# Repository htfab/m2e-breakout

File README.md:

# Caravel M.2 breakout

Minimalist breakout board for
[M.2 E-key daughtercards](https://github.com/efabless/caravel_board/tree/main/hardware/breakout/caravel-M.2-card-QFN)
shipped with OpenMPW/chipIgnite ICs.

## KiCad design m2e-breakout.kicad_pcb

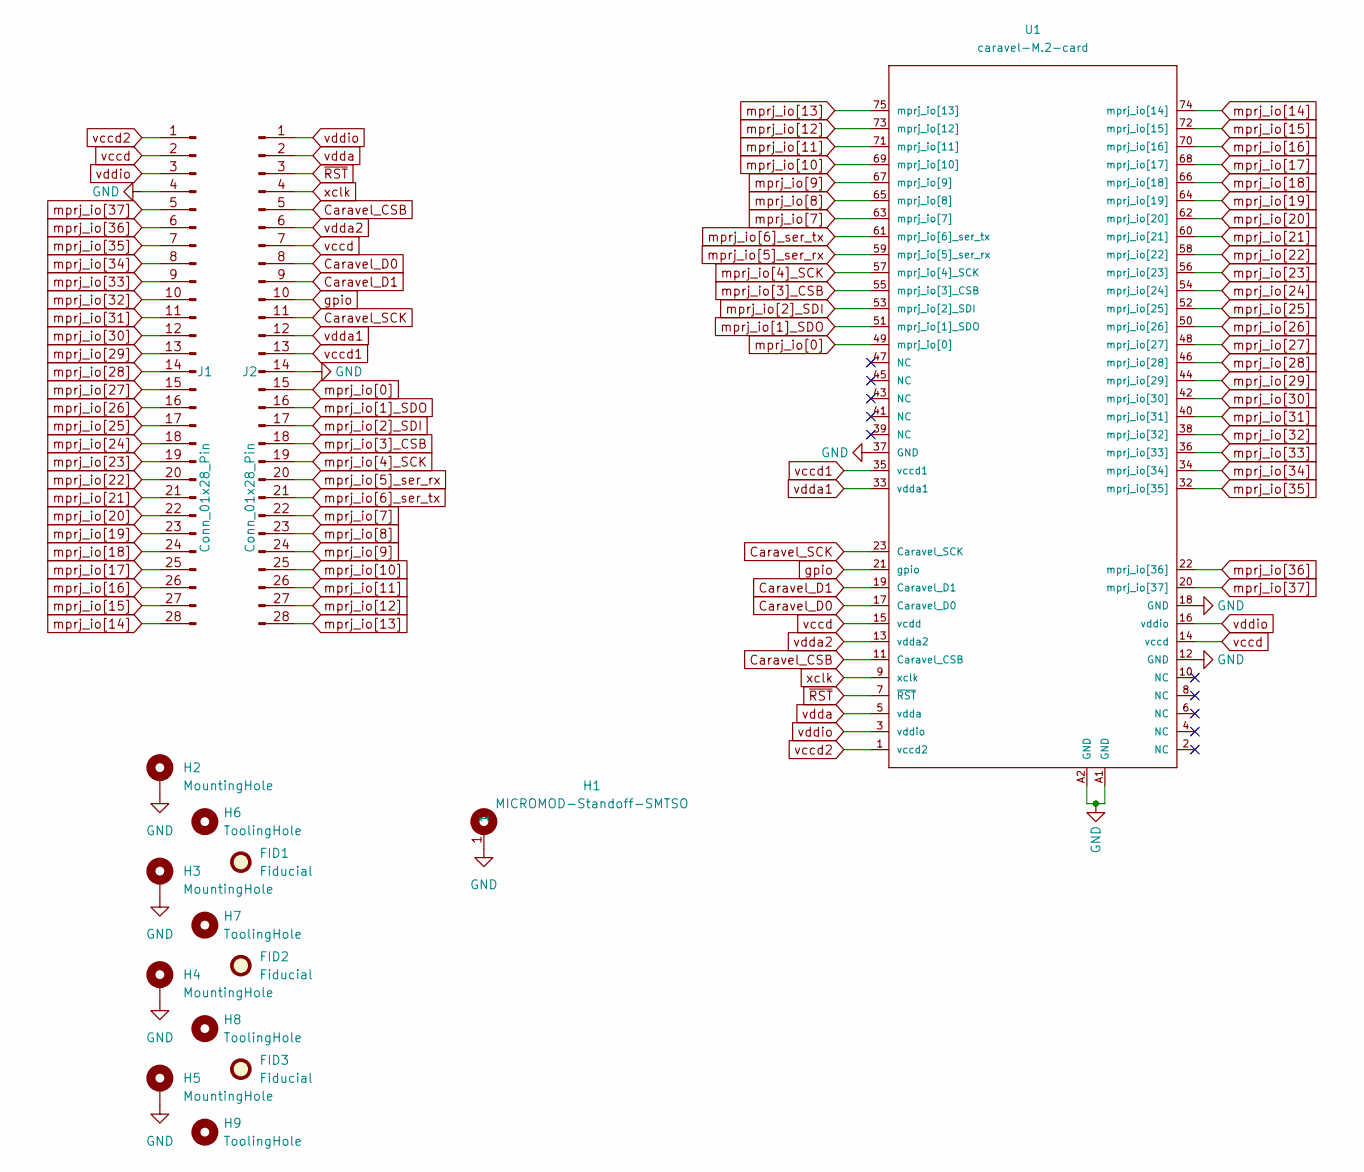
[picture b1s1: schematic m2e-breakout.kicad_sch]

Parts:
FID1, FID2, FID3: Fiducial; Fiducial_1mm_Mask3mm
H1: MICROMOD-Standoff-SMTSO; MicroMod-Standoff-SMTSO; LCSC C2915630
H2, H3, H4, H5: MountingHole; MountingHole_2.7mm_M2.5_Pad_Via
H6, H7, H8, H9: ToolingHole; ToolingHole-JLCSMT
J1, J2: Conn_01x28_Pin; PinHeader_1x28_P2.54mm_Vertical
U1: caravel-M.2-card; M.2-CONNECTOR-E; LCSC C7498141

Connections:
Caravel_CSB: J2.5, U1.11 (Caravel_CSB)
Caravel_D0: J2.8, U1.17 (Caravel_D0)
Caravel_D1: J2.9, U1.19 (Caravel_D1)
Caravel_SCK: J2.11, U1.23 (Caravel_SCK)
GND: H1.1, H2.1, H3.1, H4.1, H5.1, J1.4, J2.14, U1.12 (GND), U1.18 (GND), U1.37 (GND), U1.A1 (GND), U1.A2 (GND)
gpio: J2.10, U1.21 (gpio)
mprj_io[0]: J2.15, U1.49 (mprj_io[0])
mprj_io[1]_SDO: J2.16, U1.51 (mprj_io[1]_SDO)
mprj_io[2]_SDI: J2.17, U1.53 (mprj_io[2]_SDI)
mprj_io[3]_CSB: J2.18, U1.55 (mprj_io[3]_CSB)
mprj_io[4]_SCK: J2.19, U1.57 (mprj_io[4]_SCK)
mprj_io[5]_ser_rx: J2.20, U1.59 (mprj_io[5]_ser_rx)
mprj_io[6]_ser_tx: J2.21, U1.61 (mprj_io[6]_ser_tx)
mprj_io[7]: J2.22, U1.63 (mprj_io[7])
mprj_io[8]: J2.23, U1.65 (mprj_io[8])
mprj_io[9]: J2.24, U1.67 (mprj_io[9])
mprj_io[10]: J2.25, U1.69 (mprj_io[10])
mprj_io[11]: J2.26, U1.71 (mprj_io[11])
mprj_io[12]: J2.27, U1.73 (mprj_io[12])
mprj_io[13]: J2.28, U1.75 (mprj_io[13])
mprj_io[14]: J1.28, U1.74 (mprj_io[14])
mprj_io[15]: J1.27, U1.72 (mprj_io[15])
mprj_io[16]: J1.26, U1.70 (mprj_io[16])
mprj_io[17]: J1.25, U1.68 (mprj_io[17])
mprj_io[18]: J1.24, U1.66 (mprj_io[18])
mprj_io[19]: J1.23, U1.64 (mprj_io[19])
mprj_io[20]: J1.22, U1.62 (mprj_io[20])
mprj_io[21]: J1.21, U1.60 (mprj_io[21])
mprj_io[22]: J1.20, U1.58 (mprj_io[22])
mprj_io[23]: J1.19, U1.56 (mprj_io[23])
mprj_io[24]: J1.18, U1.54 (mprj_io[24])
mprj_io[25]: J1.17, U1.52 (mprj_io[25])
mprj_io[26]: J1.16, U1.50 (mprj_io[26])
mprj_io[27]: J1.15, U1.48 (mprj_io[27])
mprj_io[28]: J1.14, U1.46 (mprj_io[28])
mprj_io[29]: J1.13, U1.44 (mprj_io[29])
mprj_io[30]: J1.12, U1.42 (mprj_io[30])
mprj_io[31]: J1.11, U1.40 (mprj_io[31])
mprj_io[32]: J1.10, U1.38 (mprj_io[32])
mprj_io[33]: J1.9, U1.36 (mprj_io[33])
mprj_io[34]: J1.8, U1.34 (mprj_io[34])
mprj_io[35]: J1.7, U1.32 (mprj_io[35])
mprj_io[36]: J1.6, U1.22 (mprj_io[36])
mprj_io[37]: J1.5, U1.20 (mprj_io[37])
vccd: J1.2, J2.7, U1.14 (vccd), U1.15 (vcdd)
vccd1: J2.13, U1.35 (vccd1)
vccd2: J1.1, U1.1 (vccd2)
vdda: J2.2, U1.5 (vdda)
vdda1: J2.12, U1.33 (vdda1)
vdda2: J2.6, U1.13 (vdda2)
vddio: J1.3, J2.1, U1.3 (vddio), U1.16 (vddio)
xclk: J2.4, U1.9 (xclk)
~RST: J2.3, U1.7 (~RST)

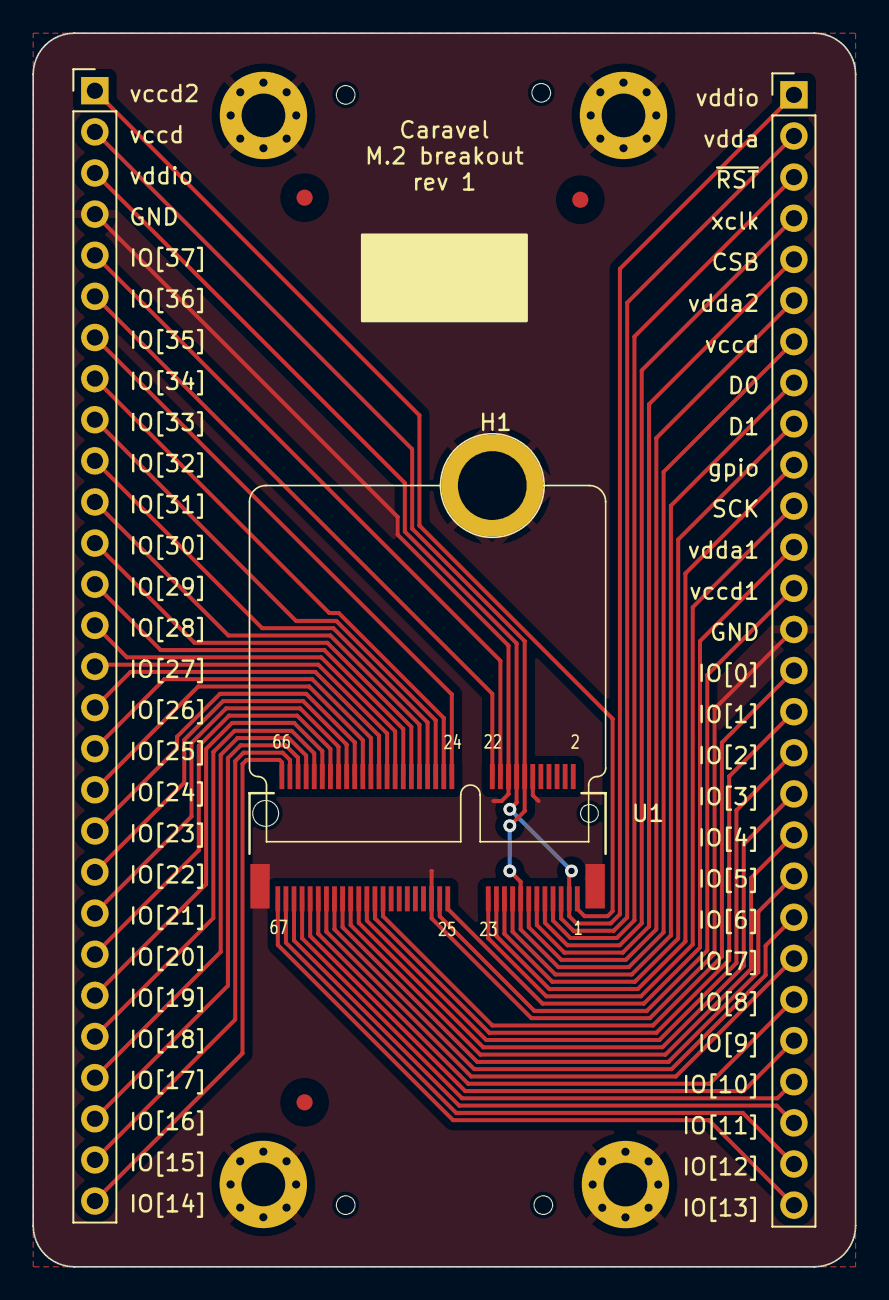
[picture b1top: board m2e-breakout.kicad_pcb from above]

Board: 2 copper layers, 50.8 x 76.2 mm, 15 parts (0 on the bottom side), 53 nets.

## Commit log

2024-01-24 add project to version control
